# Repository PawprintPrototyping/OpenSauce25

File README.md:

# OpenSauce25
All things Open Sauce 2025

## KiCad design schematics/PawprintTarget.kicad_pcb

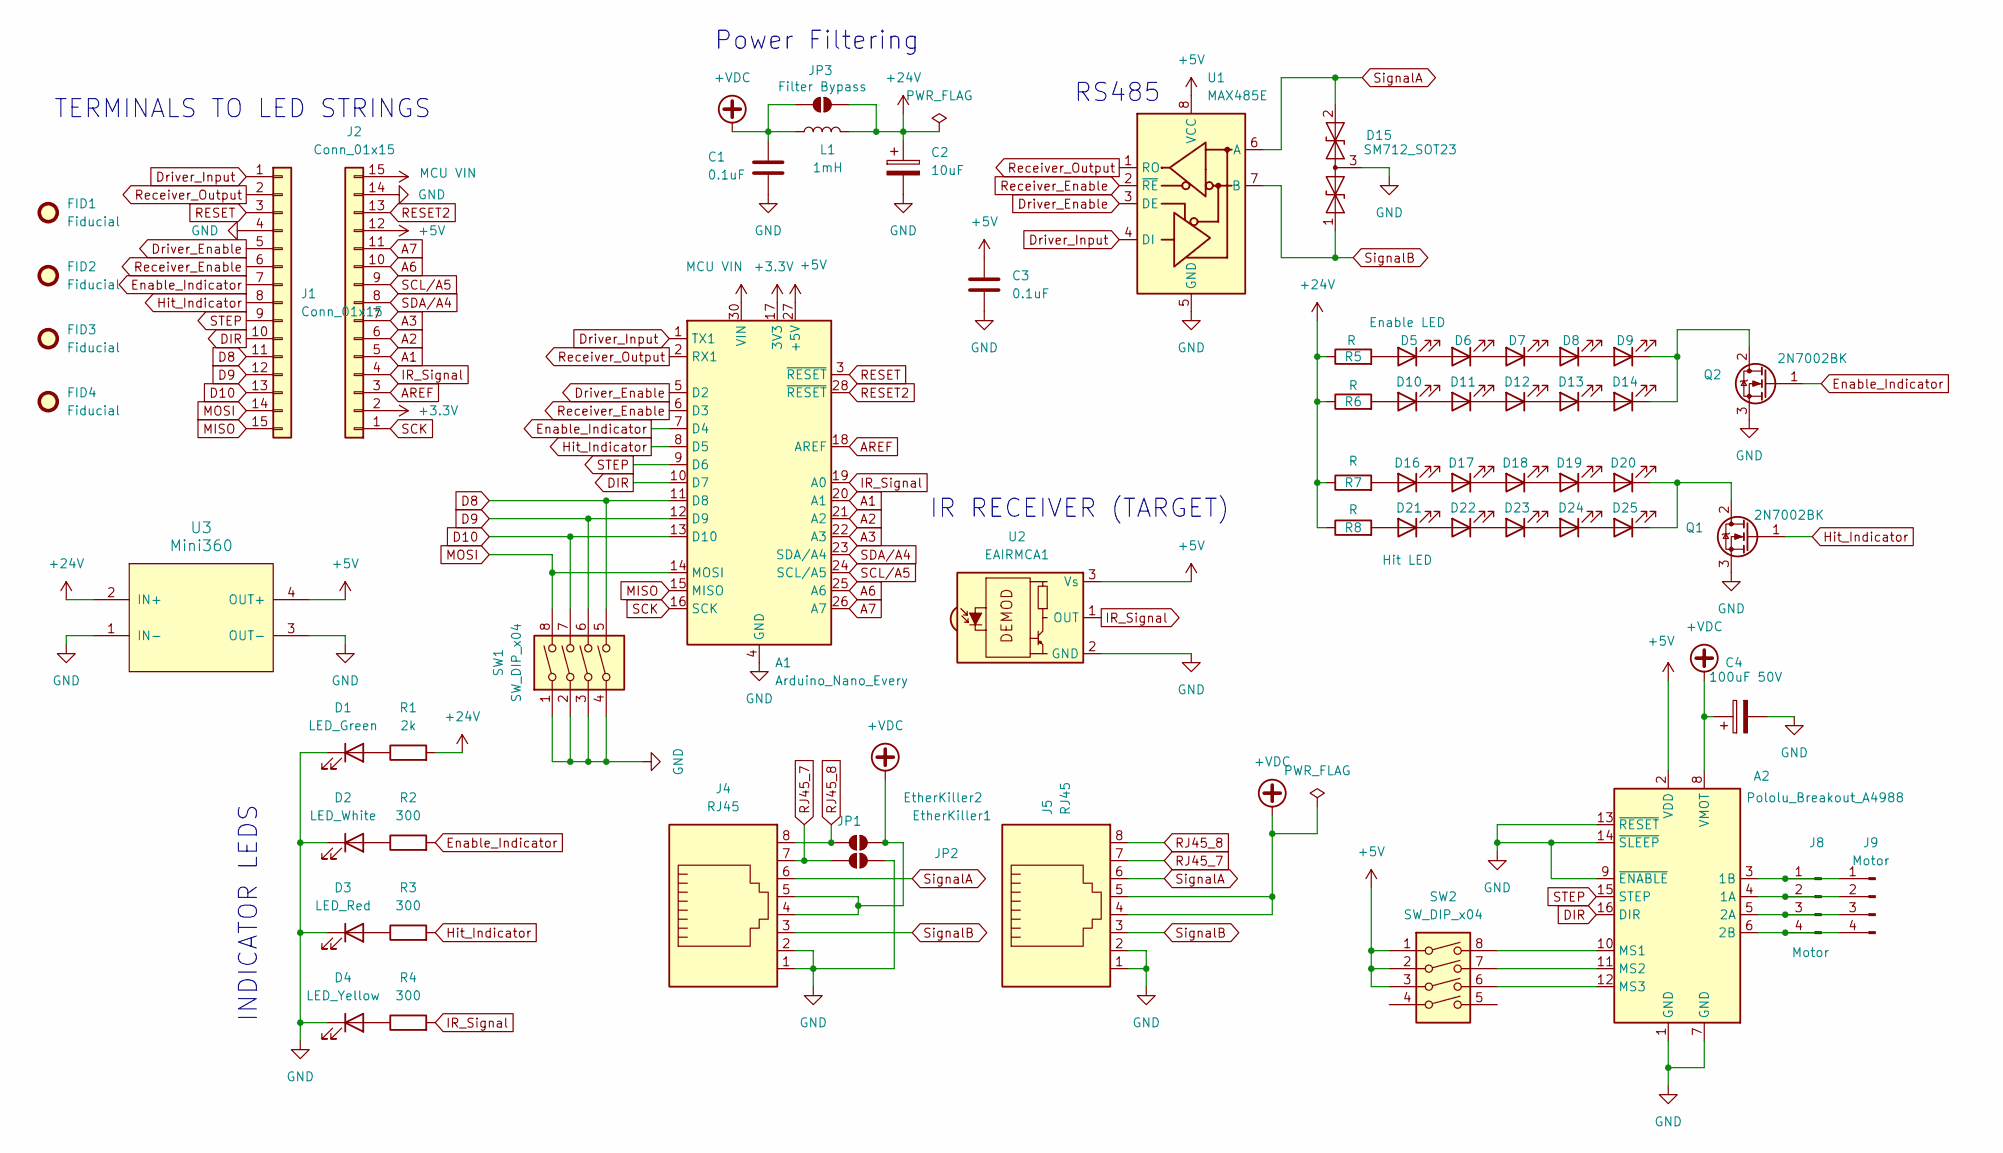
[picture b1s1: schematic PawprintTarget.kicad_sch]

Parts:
A1: Arduino_Nano_Every; Arduino_Nano
A2: Pololu_Breakout_A4988; Pololu_Breakout-16_15.2x20.3mm
C1, C3: 0.1uF; C_0805_2012Metric
C2: 10uF; C_1206_3216Metric
C4: 100uF 50V; CP_Elec_10x10.5
D1: LED_Green; LED_1206_3216Metric
D2: LED_White; LED_1206_3216Metric
D3: LED_Red; LED_1206_3216Metric
D4: LED_Yellow; LED_1206_3216Metric
D5, D6, D7, D8, D9, D10, D11, D12, D13, D14: Enable LED; LED_1206_3216Metric
D15: SM712_SOT23; SOT-23
D16, D17, D18, D19, D20, D21, D22, D23, D24, D25: Hit LED; LED_1206_3216Metric
FID1, FID2, FID3, FID4: Fiducial; Fiducial_1mm_Mask2mm
J1, J2: Conn_01x15; PinSocket_1x15_P2.54mm_Vertical
J4, J5: RJ45; RJ45_Amphenol_54602-x08_Horizontal
J8: Motor; PinSocket_1x04_P2.54mm_Vertical
J9: Motor; JST_PH_B4B-PH-K_1x04_P2.00mm_Vertical
JP1: EtherKiller1; SolderJumper-2_P1.3mm_Open_TrianglePad1.0x1.5mm
JP2: EtherKiller2; SolderJumper-2_P1.3mm_Open_TrianglePad1.0x1.5mm
JP3: Filter Bypass; SolderJumper-2_P1.3mm_Open_TrianglePad1.0x1.5mm
L1: 1mH; Inductor_SDR1307
Q1, Q2: 2N7002BK; SOT-23-3
R1: 2k; R_0603_1608Metric
R2, R3, R4: 300; R_0603_1608Metric
R5, R6, R7, R8: R; R_0603_1608Metric
SW1, SW2: SW_DIP_x04; SW_DIP_SPSTx04_Piano_10.8x11.72mm_W7.62mm_P2.54mm
U1: MAX485E; SOIC-8_3.9x4.9mm_P1.27mm
U2: EAIRMCA1; Vishay_MOLD-3Pin
U3: Mini360; Mini360_step-down

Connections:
+3.3V: A1.17 (3V3), J2.2
+5V: A1.27 (+5V), A2.2 (VDD), C3.1, J2.12, SW2.1, SW2.2, SW2.3, U1.8 (VCC), U2.3 (Vs), U3.4 (OUT+)
+24V: C2.1, JP3.2 (B), L1.2, R1.2, R5.1, R6.1, R7.1, R8.1, U3.2 (IN+)
+VDC: A2.8 (VMOT), C1.1, C4.1, J4.4, J4.5, J5.4, J5.5, JP2.2 (B), JP3.1 (A), L1.1
A1: A1.20 (A1), J2.5
A2: A1.21 (A2), J2.6
A3: A1.22 (A3), J2.7
A6: A1.25 (A6), J2.10
A7: A1.26 (A7), J2.11
AREF: A1.18 (AREF), J2.3
D8: A1.11 (D8), J1.11, SW1.5
D9: A1.12 (D9), J1.12, SW1.6
D10: A1.13 (D10), J1.13, SW1.7
DIR: A1.10 (D7), A2.16 (DIR), J1.10
Driver_Enable: A1.5 (D2), J1.5, U1.3 (DE)
Driver_Input: A1.1 (TX1), J1.1, U1.4 (DI)
Enable_Indicator: A1.7 (D4), J1.7, Q2.1 (G), R2.2
GND: A1.4 (GND), A1.29 (GND), A2.1 (GND), A2.7 (GND), A2.9 (~ENABLE), A2.13 (~RESET), A2.14 (~SLEEP), C1.2, C2.2, C3.2, C4.2, D1.1 (K), D2.1 (K), D3.1 (K), D4.1 (K), D15.3 (common), J1.4, J2.14, J4.1, J4.2, J5.1, J5.2, JP1.2 (B), Q1.3 (S), Q2.3 (S), SW1.1, SW1.2, SW1.3, SW1.4, U1.5 (GND), U2.2 (GND), U3.1 (IN-), U3.3 (OUT-)
Hit_Indicator: A1.8 (D5), J1.8, Q1.1 (G), R3.2
IR_Signal: A1.19 (A0), J2.4, R4.2, U2.1 (OUT)
MCU VIN: A1.30 (VIN), J2.15
MISO: A1.15 (MISO), J1.15
MOSI: A1.14 (MOSI), J1.14, SW1.8
unnamed: A2.4 (1A), J8.2, J9.2
unnamed: A2.3 (1B), J8.1, J9.1
unnamed: A2.5 (2A), J8.3, J9.3
unnamed: A2.6 (2B), J8.4, J9.4
unnamed: A2.10 (MS1), SW2.8
unnamed: A2.11 (MS2), SW2.7
unnamed: A2.12 (MS3), SW2.6
unnamed: D1.2 (A), R1.1
unnamed: D2.2 (A), R2.1
unnamed: D3.2 (A), R3.1
unnamed: D4.2 (A), R4.1
unnamed: D5.2 (A), R5.2
unnamed: D5.1 (K), D6.2 (A)
unnamed: D6.1 (K), D7.2 (A)
unnamed: D7.1 (K), D8.2 (A)
unnamed: D8.1 (K), D9.2 (A)
unnamed: D10.2 (A), R6.2
unnamed: D10.1 (K), D11.2 (A)
unnamed: D11.1 (K), D12.2 (A)
unnamed: D12.1 (K), D13.2 (A)
unnamed: D13.1 (K), D14.2 (A)
unnamed: D9.1 (K), D14.1 (K), Q2.2 (D)
unnamed: D16.2 (A), R7.2
unnamed: D16.1 (K), D17.2 (A)
unnamed: D17.1 (K), D18.2 (A)
unnamed: D18.1 (K), D19.2 (A)
unnamed: D19.1 (K), D20.2 (A)
unnamed: D20.1 (K), D25.1 (K), Q1.2 (D)
unnamed: D21.2 (A), R8.2
unnamed: D21.1 (K), D22.2 (A)
unnamed: D22.1 (K), D23.2 (A)
unnamed: D23.1 (K), D24.2 (A)
unnamed: D24.1 (K), D25.2 (A)
RESET: A1.3 (~RESET), J1.3
RESET2: A1.28 (~RESET), J2.13
RJ45_7: J4.7, J5.7, JP1.1 (A)
RJ45_8: J4.8, J5.8, JP2.1 (A)
Receiver_Enable: A1.6 (D3), J1.6, U1.2 (~RE)
Receiver_Output: A1.2 (RX1), J1.2, U1.1 (RO)
SCK: A1.16 (SCK), J2.1
SCL/A5: A1.24 (SCL/A5), J2.9
SDA/A4: A1.23 (SDA/A4), J2.8
STEP: A1.9 (D6), A2.15 (STEP), J1.9
SignalA: D15.2 (A2), J4.6, J5.6, U1.6 (A)
SignalB: D15.1 (A1), J4.3, J5.3, U1.7 (B)

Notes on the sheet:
TERMINALS TO LED STRINGS
RS485
Power Filtering
IR RECEIVER (TARGET)
INDICATOR LEDS

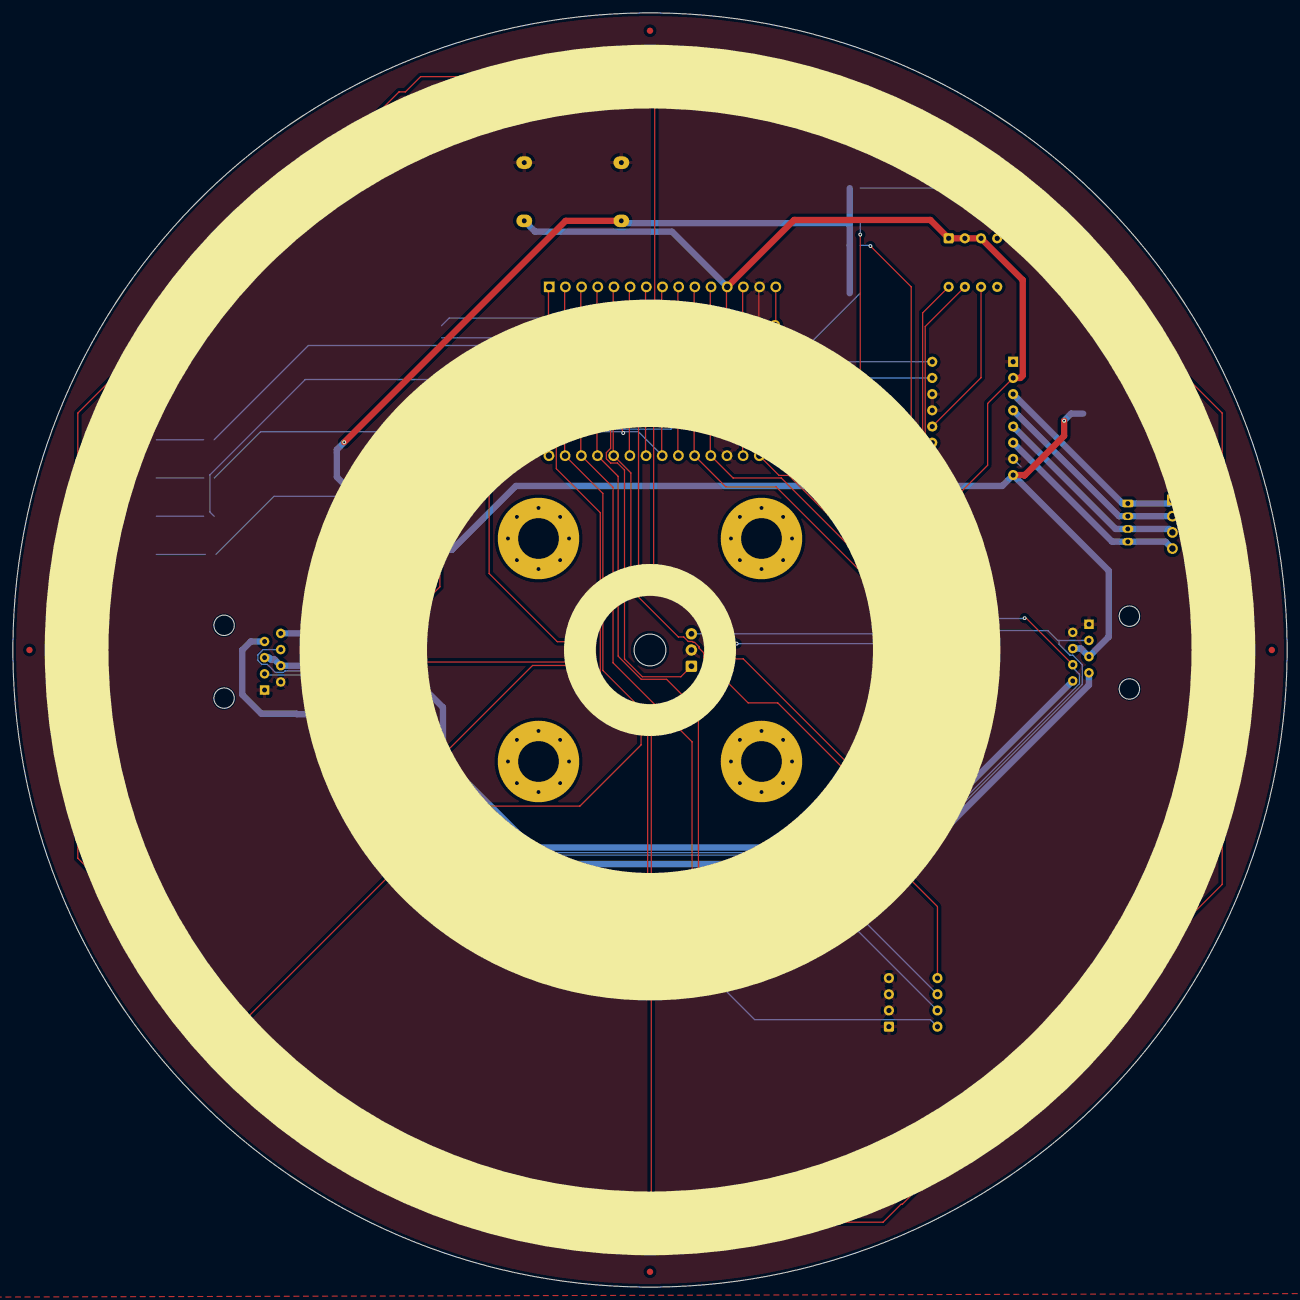
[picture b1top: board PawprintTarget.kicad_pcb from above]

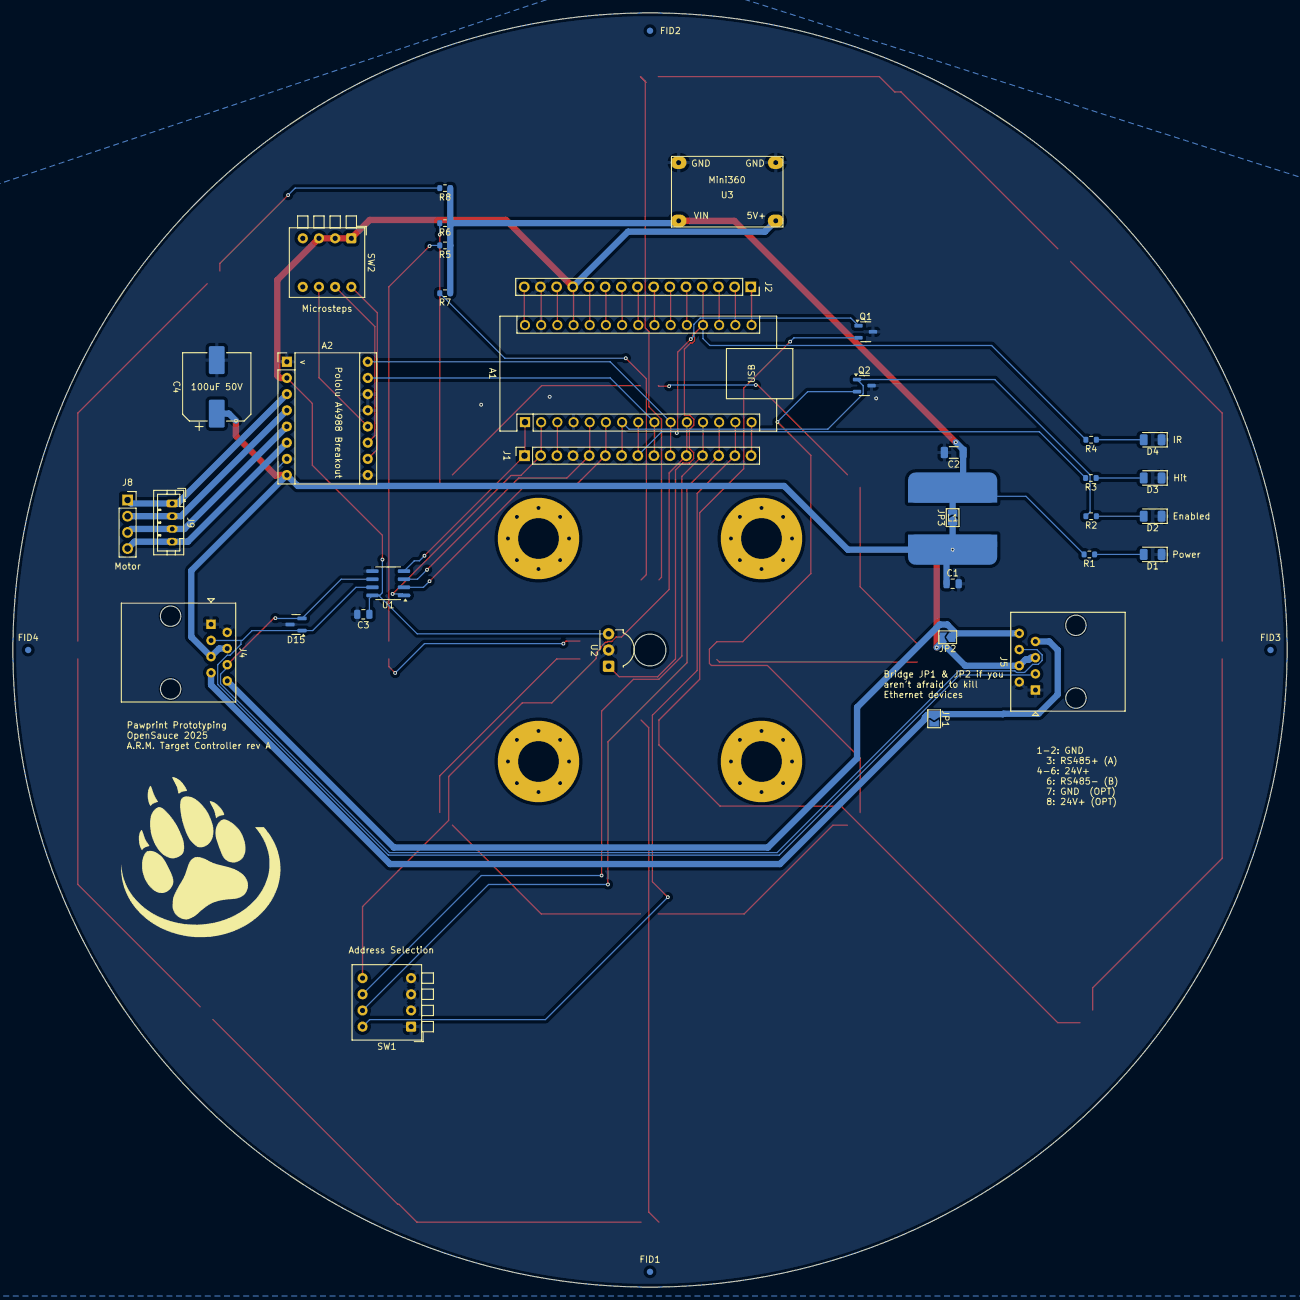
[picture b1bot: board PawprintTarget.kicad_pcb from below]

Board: 2 copper layers, 200.0 x 200.0 mm, 64 parts (40 on the bottom side), 68 nets.

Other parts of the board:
FID1#2, FID2#2, FID3#2, FID4#2: Fiducial; Fiducial_1mm_Mask2mm

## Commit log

2025-02-19 Created everything
2025-02-20 Created Schematic for PawChinko LED Boards
2025-04-03 Cake stuff
2025-04-04 Final cake
2025-06-20 Add target PCB design
2025-06-29 Component placements finished
2025-06-29 FreeCAD horror show
2025-06-30 Fix RJ45 connector
2025-06-30 Remove lock files
2025-06-30 Done, probably
    - Nicer labels
    - Probably won't blow up
2025-06-30 Ignore backup files
2025-06-30 Add github action to generate KiCAD output
2025-06-30 Update workflow paths
2025-06-30 Third time's the charm?
2025-06-30 Fix ERC errors
2025-06-30 Fooling around
2025-07-01 What the hell is going on
2025-07-01 Extremely frustrating
2025-07-01 Maybe it's the table?
2025-07-01 stupid
2025-07-01 Sanity
2025-07-01 Add panelized version, revise LED resistor values
2025-07-02 Final panelized version
2025-07-02 Oh my god I'm so stupid
2025-07-08 More FreeCAD nightmares
2025-07-08 Add interactive BOM
